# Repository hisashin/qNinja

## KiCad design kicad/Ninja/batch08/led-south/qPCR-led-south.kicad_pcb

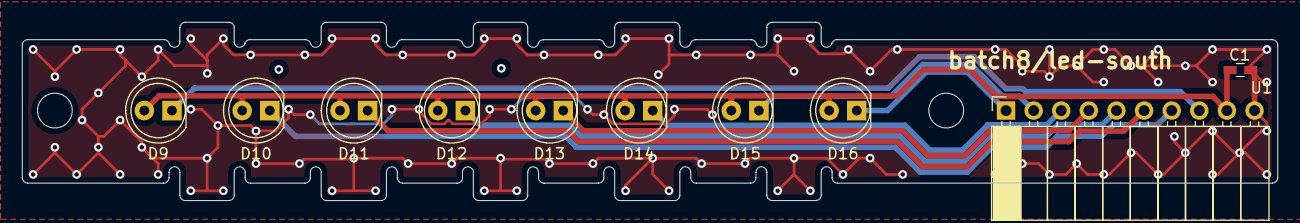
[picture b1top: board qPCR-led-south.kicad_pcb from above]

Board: 2 copper layers, 115.5 x 16.4 mm, 10 parts (0 on the bottom side), 10 nets.

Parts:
C1: C; C_0603_HandSoldering
D9, D10, D11, D12, D13, D14, D15, D16: LED; LED_D5.0mm
U1: Conn_02x05; Socket_Strip_Angled_1x10_Pitch2.54mm

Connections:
GND: C1.2, U1.10
OUT9: D9.1, U1.8
OUT10: D10.1, U1.7
OUT11: D11.1, U1.6
OUT12: D12.1, U1.5
OUT13: D13.1, U1.4
OUT14: D14.1, U1.3
OUT15: D15.1, U1.2
OUT16: D16.1, U1.1
VCC: C1.1, D9.2, D10.2, D11.2, D12.2, D13.2, D14.2, D15.2, D16.2, U1.9

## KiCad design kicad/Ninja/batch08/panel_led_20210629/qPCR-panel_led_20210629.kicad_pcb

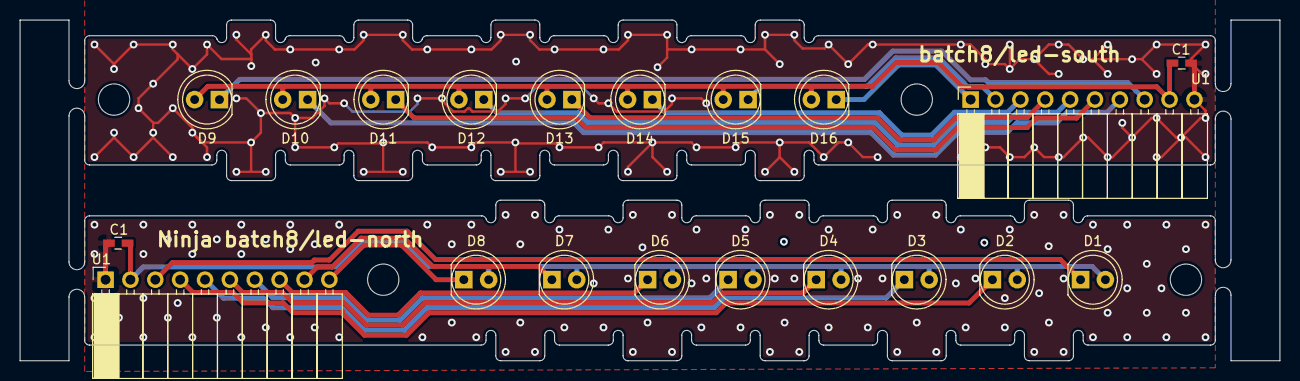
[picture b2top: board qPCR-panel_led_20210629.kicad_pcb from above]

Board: 2 copper layers, 128.7 x 34.8 mm, 20 parts (0 on the bottom side), 18 nets.

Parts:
C1, C1#2: C; C_0603_HandSoldering
D1, D2, D3, D4, D5, D6, D7, D8, D9, D10, D11, D12, D13, D14, D15, D16: LED; LED_D5.0mm
U1, U1#2: Conn_02x05; Socket_Strip_Angled_1x10_Pitch2.54mm

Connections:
GND: C1.2, C1#2.2, U1.1, U1#2.10
OUT1: D1.1, U1.3
OUT2: D2.1, U1.4
OUT3: D3.1, U1.5
OUT4: D4.1, U1.6
OUT5: D5.1, U1.7
OUT6: D6.1, U1.8
OUT7: D7.1, U1.9
OUT8: D8.1, U1.10
OUT9: D9.1, U1#2.8
OUT10: D10.1, U1#2.7
OUT11: D11.1, U1#2.6
OUT12: D12.1, U1#2.5
OUT13: D13.1, U1#2.4
OUT14: D14.1, U1#2.3
OUT15: D15.1, U1#2.2
OUT16: D16.1, U1#2.1
VCC: C1.1, C1#2.1, D1.2, D2.2, D3.2, D4.2, D5.2, D6.2, D7.2, D8.2, D9.2, D10.2, D11.2, D12.2, D13.2, D14.2, D15.2, D16.2, U1.2, U1#2.9

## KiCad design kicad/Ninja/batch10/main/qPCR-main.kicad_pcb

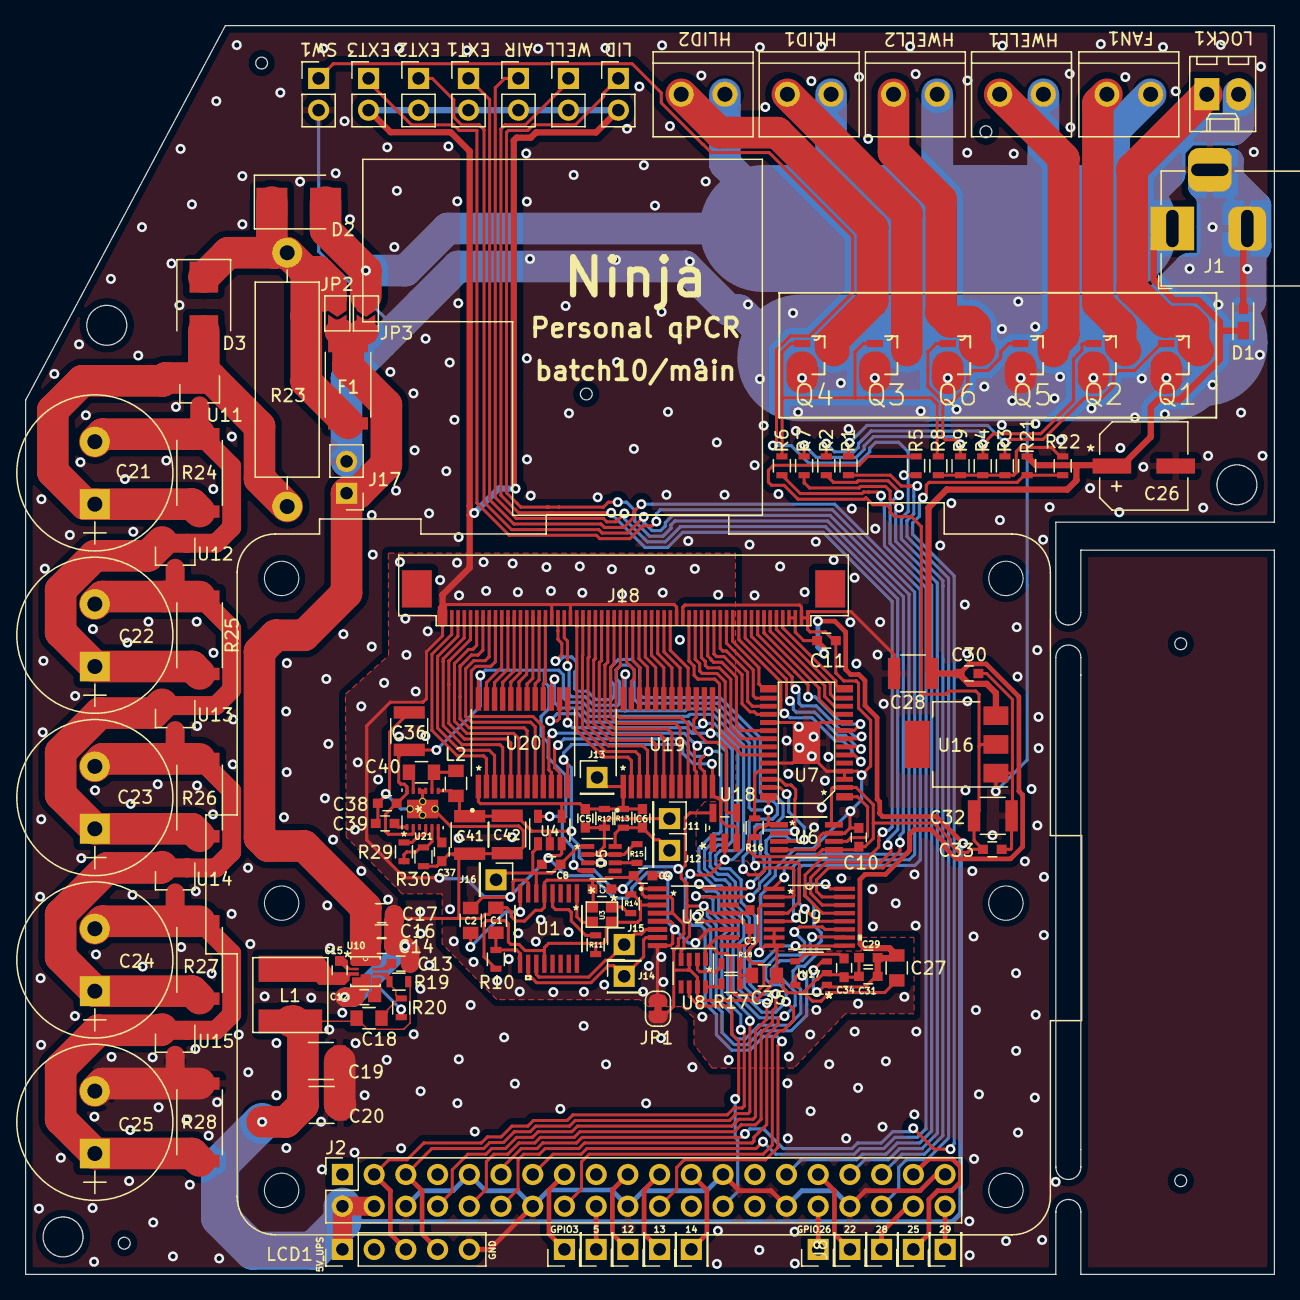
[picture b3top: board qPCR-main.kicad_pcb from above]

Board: 2 copper layers, 100.0 x 100.0 mm, 141 parts (0 on the bottom side), 134 nets.

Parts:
AIR: Conn_01x02_Male; Pin_Header_Straight_1x02_Pitch2.54mm
C1, C2, C27, C35: 4.7uF; C_0805
C3, C4, C7, C8, C10, C11, C14, C15, C29, C30, C33: 0.1uF; C_0603
C5, C6: 22pF; C_0603
C12: 1000pF; C_0603
C13, C37, C38, C39: 1uF; C_0603
C16: 10uF; C_0603
C17, C40: 10uF; C_0805
C18: DNP; C_0805
C19, C20, C28, C32, C36, C41, C42: 22uF; C_1210
C21, C22, C23, C24, C25: 10F2.7V; CP_Radial_D12.5mm_P5.00mm
C26: 100uF; 35TZV100M6.3X8
C31: 0.01uF; C_0603
C34: 100pF; C_0603
D1: D_Schottky; MSS1P3L-M3&slash_89A
D2, D3: D; D_SMB
EXT1, EXT2, EXT3: Conn_01x02_Male; Pin_Header_Straight_1x02_Pitch2.54mm
F1: Fuse; R_2512
FAN1: Screw_Terminal_01x02; TB_SeeedOPL_320110028
HLID1, HLID2: Screw_Terminal_01x02; TB_SeeedOPL_320110028
HWELL1, HWELL2: Screw_Terminal_01x02; TB_SeeedOPL_320110028
J1: Barrel_Jack_Switch; BarrelJack_Horizontal
J2: Raspberry_Pi_3A_Plus_wpi; Raspberry_Pi_3A+_3B+_4B_Zero_FaceDown_HDMI-R
J3, J4, J5, J6, J7, J8, J9, J10, J11, J12, J13, J14, J15, J16, J19, J20: Conn_01x01_Male; Pin_Header_Straight_1x01_Pitch2.54mm
J17: Conn_01x02_Male; Pin_Header_Straight_1x02_Pitch2.54mm
J18: Conn_01x60_Male; FFC_60_Ali_HUISHUNFA
JP1: SolderJumper_2_Bridged; SolderJumper-2_P1.3mm_Bridged_RoundedPad1.0x1.5mm
JP2, JP3: Jumper; SolderJumper-2_P1.3mm_Open_TrianglePad1.0x1.5mm
L1: 3.3uH; VLS6045EX-3R3N
L2: 2.2uH; C_0805
LCD1: RPI_LCD_TOUCH_7INCH; Pin_Header_Straight_1x05_Pitch2.54mm
LID: Conn_01x02_Male; Pin_Header_Straight_1x02_Pitch2.54mm
LOCK1: Conn_01x02_Male; Molex_KK-6410-02_02x2.54mm_Straight
Q1, Q2, Q3, Q4, Q5, Q6: Q_NMOS_GSD; SOT95P240X112-3N
R1, R2, R6, R7: 150; R_0603
R3, R4, R5, R8, R9, R16, R18, R21: 47k; R_0603
R10, R11, R14, R15, R17, R20, R22: 10k; R_0603
R12: 10M; R_0603
R13: 1M; R_0603
R19: 56k; R_0603
R23: 8.2Ω 3W; R_Axial_DIN0516_L15.5mm_D5.0mm_P20.32mm_Horizontal
R24, R25, R26, R27, R28: 1k2W; R_2512
R29: 39k; R_0603
R30: 150k; R_0603
SW1: SW_Reed; Pin_Header_Straight_1x02_Pitch2.54mm
U1: ADA2200ARUZ
U2: ADS122C04IPWR
U3: COM1305-0.032768-EXT-T-TR; ASDK-32.768KHZ-LRT
U4: LMP7717MF_NOPB; SOT-23-5
U5, U8: TS12A12511DCNR; SOT-23-8
U6: MCP4551T-503E/MS; MCP4551T-502E&slash_MS
U7: PCA9955B
U9: SN74LV4051APWR
U10: UMMP008Z2020_ROM; BD9D323QWZ-E2
U11, U12, U13, U14, U15: TL431DBZ; SOT-23
U16: CJT1117-3.3; SOT-223
U17: AP2210K-3.3TRG1
U18: SN74LVC1GU04DCKR; SN74LVC1GU04DBVR
U19, U20: CD74HC4067M96; SOP65P780X200-24N
U21: DRR0012C; TPS63710DRRR
WELL: Conn_01x02_Male; Pin_Header_Straight_1x02_Pitch2.54mm

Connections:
3V3A: C3.1, C35.1, R17.1, R18.1, U2.9, U2.12, U17.5
3V3D: C3.2, C7.1, C10.1, C32.1, C33.1, C36.1, C38.1, R5.1, R10.2, R11.2, R14.2, R16.2, U1.12, U2.3, U2.13, U3.4, U4.5, U5.4, U6.1, U6.5, U6.8, U7.2, U7.28, U8.4, U9.16, U16.2, U18.5, U19.24, U20.24, U21.2, U21.12
5V_UPS: C11.1, C18.2, C19.2, C20.2, J2.2, J2.4, J18.3, J18.4, L1.1, LCD1.1, R19.1
12V: C26.1, C27.1, C28.1, C29.1, C30.1, C31.1, D1.1, D2.2, FAN1.1, HLID1.1, HLID2.1, HWELL1.1, HWELL2.1, J1.1, JP3.1, LOCK1.2, R21.1, U16.3, U17.1, U17.3
12V_UPS: C14.2, C16.2, C17.2, F1.1, J17.1, JP2.2, JP3.2, U10.1, U10.8
-1V: C41.1, C42.1, L2.2, R15.2, U4.2, U5.3, U5.7, U18.3, U19.12, U20.12, U21.7
/5V_UPS/FB: C18.1, R19.2, R20.1, U10.6
/5V_UPS/SS: C12.2, U10.5
/FAN: J2.29, R2.2
/GPIO3: J2.15, J3.1
/GPIO5: J2.18, J4.1
/GPIO12: J2.19, J5.1
/GPIO13: J2.21, J6.1
/GPIO14: J2.23, J7.1
/GPIO22: J2.31, J8.1
/GPIO25: J2.37, J19.1
/GPIO26: J2.32, J9.1
/GPIO28: J2.38, J10.1
/GPIO29: J2.40, J20.1
/LID_HEATER: J2.13, R6.2
/Photo/AMP_GAIN_SW: R15.1, U5.6
/Photo/AMP_OUT: C8.2, J16.1, U1.6, U4.1, U5.1
/Photo/GAIN_LARGE: C5.1, J11.1, R12.2, U5.2
/Photo/GAIN_SMALL: C6.1, J12.1, R13.2, U5.8
/Photo/PHOTO_OUT_N: J14.1, U1.10, U2.7
/Photo/PHOTO_OUT_P: J15.1, U1.11, U2.6
/PhotoLED/LED_IREF: U6.6, U7.1
/PhotoMUX/MUX_SELECT_INV: U18.4, U19.15
/PhotoMUX/N_PD_OUT1: J18.43, U20.16
/PhotoMUX/N_PD_OUT2: J18.44, U20.17
/PhotoMUX/N_PD_OUT3: J18.45, U20.18
/PhotoMUX/N_PD_OUT4: J18.46, U20.19
/PhotoMUX/N_PD_OUT5: J18.47, U20.20
/PhotoMUX/N_PD_OUT6: J18.48, U20.21
/PhotoMUX/N_PD_OUT7: J18.49, U20.22
/PhotoMUX/N_PD_OUT8: J18.50, U20.23
/PhotoMUX/N_PD_OUT9: J18.51, U20.9
/PhotoMUX/N_PD_OUT10: J18.52, U20.8
/PhotoMUX/N_PD_OUT11: J18.53, U20.7
/PhotoMUX/N_PD_OUT12: J18.54, U20.6
/PhotoMUX/N_PD_OUT13: J18.55, U20.5
/PhotoMUX/N_PD_OUT14: J18.56, U20.4
/PhotoMUX/N_PD_OUT15: J18.57, U20.3
/PhotoMUX/N_PD_OUT16: J18.58, U20.2
/PhotoMUX/S_PD_OUT1: J18.38, U19.2
/PhotoMUX/S_PD_OUT2: J18.37, U19.3
/PhotoMUX/S_PD_OUT3: J18.36, U19.4
/PhotoMUX/S_PD_OUT4: J18.35, U19.5
/PhotoMUX/S_PD_OUT5: J18.34, U19.6
/PhotoMUX/S_PD_OUT6: J18.33, U19.7
/PhotoMUX/S_PD_OUT7: J18.32, U19.8
/PhotoMUX/S_PD_OUT8: J18.31, U19.9
/PhotoMUX/S_PD_OUT9: J18.30, U19.23
/PhotoMUX/S_PD_OUT10: J18.29, U19.22
/PhotoMUX/S_PD_OUT11: J18.28, U19.21
/PhotoMUX/S_PD_OUT12: J18.27, U19.20
/PhotoMUX/S_PD_OUT13: J18.26, U19.19
/PhotoMUX/S_PD_OUT14: J18.25, U19.18
/PhotoMUX/S_PD_OUT15: J18.24, U19.17
/PhotoMUX/S_PD_OUT16: J18.23, U19.16
/WELL_HEATER: J2.33, R7.2
CLKIN: U1.1, U3.3
DLOCK: J2.36, R1.2
DOPEN: J2.35, R5.2, SW1.1
GND: C1.2, C4.2, C7.2, C10.2, C11.2, C12.1, C13.1, C14.1, C16.1, C17.1, C19.1, C20.1, C25.2, C26.2, C27.2, C28.2, C29.2, C30.2, C31.2, C32.2, C33.2, C34.2, C35.2, C36.2, C37.2, C38.2, C39.2, C41.2, C42.2, D1.2, J1.2, J1.3, J2.6, J2.9, J2.14, J2.20, J2.25, J2.30, J2.34, J2.39, J17.2, J18.1, J18.2, J18.21, JP1.1, LCD1.5, Q1.2, Q2.2, Q3.2, Q4.2, Q5.2, Q6.2, R3.1, R4.1, R8.1, R9.1, R20.2, R22.2, R28.1, R30.2, SW1.2, U1.5, U2.1, U2.2, U2.4, U3.2, U6.4, U6.7, U7.3, U7.4, U7.10, U7.19, U7.24, U7.29, U8.3, U8.7, U9.6, U9.7, U9.8, U10.4, U10.9, U15.3, U16.1, U17.2, U21.9, U21.10, U21.13, U21.V
GNDA: AIR.2, C2.2, C4.1, C8.1, EXT1.2, EXT2.2, EXT3.2, J18.22, J18.39, J18.42, J18.59, J18.60, JP1.2, LID.2, U1.7, U2.5, U2.8, U2.11, U4.3, WELL.2
I2C_SCL: J2.5, LCD1.4, U2.16, U6.2, U7.26
I2C_SDA: J2.3, LCD1.3, U2.15, U6.3, U7.27
MUX_S0: J2.16, U9.11, U19.10, U20.10
MUX_S1: J2.12, U9.10, U19.11, U20.11
MUX_S2: J2.10, U9.9, U19.14, U20.14
MUX_S3: J2.8, U19.13, U20.13
MUX_SELECT: J2.22, U18.2, U20.15
N_LED_OUT1: J18.20, U7.23
N_LED_OUT2: J18.19, U7.22
N_LED_OUT3: J18.18, U7.21
N_LED_OUT4: J18.17, U7.20
N_LED_OUT5: J18.16, U7.18
N_LED_OUT6: J18.15, U7.17
N_LED_OUT7: J18.14, U7.16
N_LED_OUT8: J18.13, U7.15
unnamed: C1.1, R10.1, U1.9
unnamed: C2.1, U1.8
unnamed: C13.2, U10.7
unnamed: C15.1, L1.2, U10.3
unnamed: C15.2, U10.2
unnamed: C21.1, D3.2, R23.1, R24.2, U11.1, U11.2
unnamed: C21.2, C22.1, R24.1, R25.2, U11.3, U12.1, U12.2
unnamed: C22.2, C23.1, R25.1, R26.2, U12.3, U13.1, U13.2
unnamed: C23.2, C24.1, R26.1, R27.2, U13.3, U14.1, U14.2
unnamed: C24.2, C25.1, R27.1, R28.2, U14.3, U15.1, U15.2
unnamed: C34.1, U17.4
unnamed: C37.1, U21.6
unnamed: C39.1, U21.1
unnamed: C40.1, U21.11
unnamed: C40.2, L2.1, U21.8
unnamed: D2.1, D3.1, F1.2, JP2.1, R23.2
unnamed: FAN1.2, Q2.3
unnamed: HLID1.2, Q3.3
unnamed: HLID2.2, Q4.3
unnamed: HWELL1.2, Q5.3
unnamed: HWELL2.2, Q6.3
unnamed: LOCK1.1, Q1.3
unnamed: Q1.1, R1.1, R3.2
unnamed: Q2.1, R2.1, R4.2
unnamed: Q3.1, Q4.1, R6.1, R8.2
unnamed: Q5.1, Q6.1, R7.1, R9.2
unnamed: R11.1, U1.4
unnamed: R14.1, U3.1
unnamed: R16.1, U7.25
unnamed: R17.2, U8.8
unnamed: R18.2, U8.2
unnamed: R29.1, U21.4
unnamed: R29.2, R30.1, U21.5
PD_MUX_OUT: C5.2, C6.2, J13.1, R12.1, R13.1, U4.4, U19.1, U20.1
PD_TH1: J18.40, U9.2
PD_TH2: J18.41, U9.4
S_LED_OUT1: J18.12, U7.6
S_LED_OUT2: J18.11, U7.7
S_LED_OUT3: J18.10, U7.8
S_LED_OUT4: J18.9, U7.9
S_LED_OUT5: J18.8, U7.11
S_LED_OUT6: J18.7, U7.12
S_LED_OUT7: J18.6, U7.13
S_LED_OUT8: J18.5, U7.14
THERM_AIR: AIR.1, U9.14
THERM_EXT1: EXT1.1, U9.12
THERM_EXT2: EXT2.1, U9.1
THERM_EXT3: EXT3.1, U9.5
THERM_LID: LID.1, U9.15
THERM_MUX_OUT: U2.10, U8.1, U9.3
THERM_R_SWITCH: J2.26, U8.6
THERM_WELL: U9.13, WELL.1
VIN_SENSE: J2.11, R21.2, R22.1

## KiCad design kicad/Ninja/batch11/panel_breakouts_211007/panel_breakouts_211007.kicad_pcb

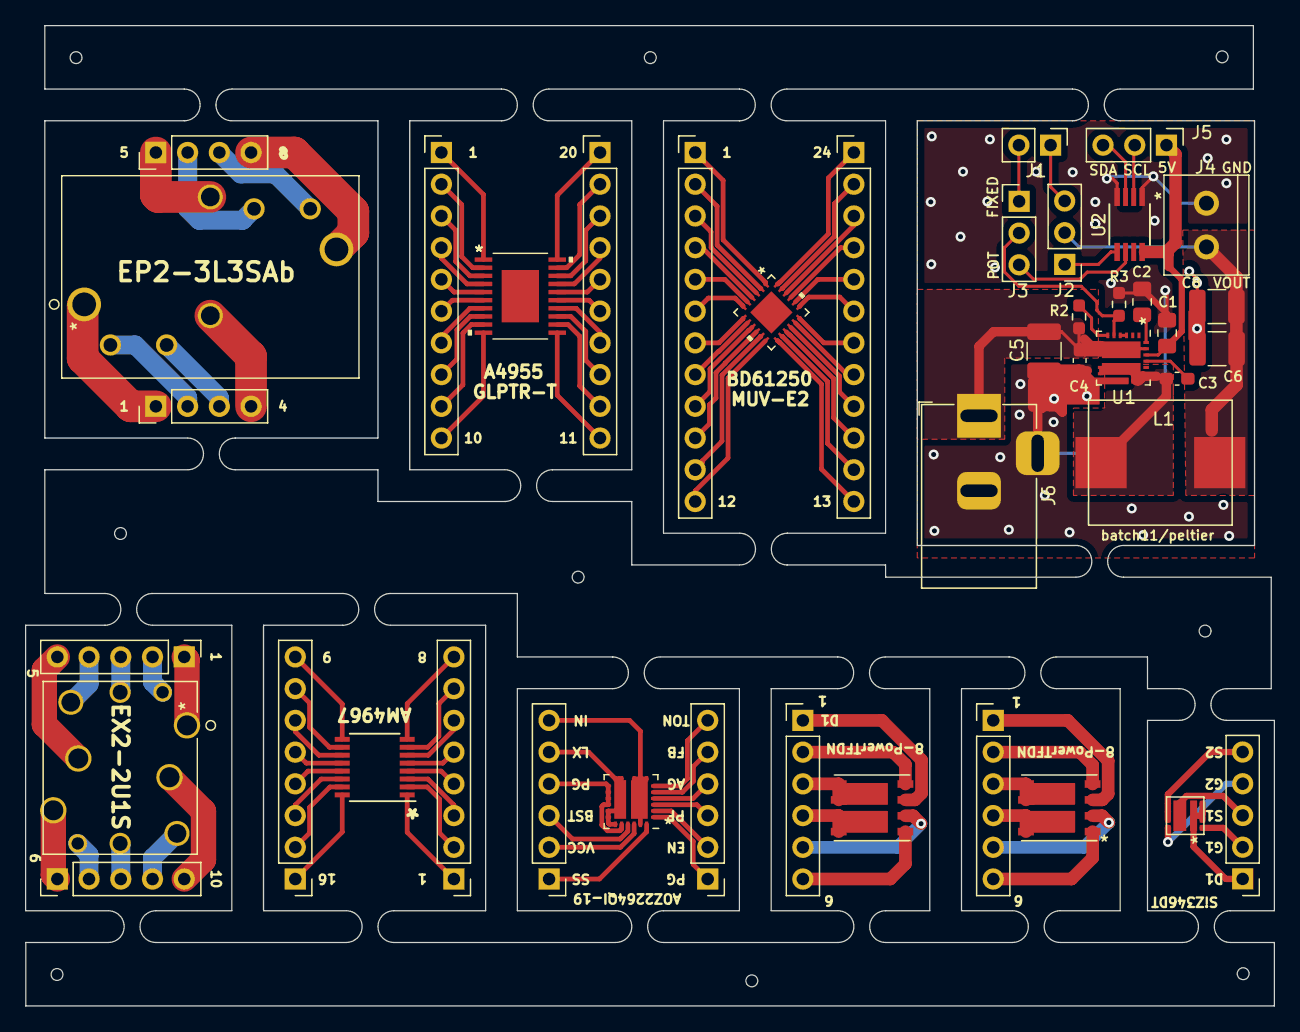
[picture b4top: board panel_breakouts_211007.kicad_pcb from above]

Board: 2 copper layers, 100.0 x 78.5 mm, 42 parts (0 on the bottom side), 122 nets.

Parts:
C1, C2: 10uF; C_0805_2012Metric_Pad1.18x1.45mm_HandSolder
C3: 0.1uF; C_0603_1608Metric_Pad1.08x0.95mm_HandSolder
C4: 1uF; C_0603_1608Metric_Pad1.08x0.95mm_HandSolder
C5: 22uF; C_1210_3225Metric_Pad1.33x2.70mm_HandSolder
C6, C8: 47uF; C_1210_3225Metric_Pad1.33x2.70mm_HandSolder
J1, J4: Conn_01x04_Male; Pin_Header_Straight_1x04_Pitch2.54mm
J1#2: Conn_01x02_Female; Pin_Header_Straight_1x02_Pitch2.54mm
J2, J3, J13: Conn_01x05_Male; Pin_Header_Straight_1x05_Pitch2.54mm
J2#2, J3#2, J5#2: Conn_01x03_Male; Pin_Header_Straight_1x03_Pitch2.54mm
J4#2: Screw_Terminal_01x02; TB_SeeedOPL_320110028
J5, J6: Conn_01x10_Male; Pin_Header_Straight_1x10_Pitch2.54mm
J6#2: Barrel_Jack_Switch; BarrelJack_Horizontal
J7, J8: Conn_01x08_Male; Pin_Header_Straight_1x08_Pitch2.54mm
J9, J10: Conn_01x12_Male; Pin_Header_Straight_1x12_Pitch2.54mm
J11, J12, J14, J15: Conn_01x06_Male; Pin_Header_Straight_1x06_Pitch2.54mm
K1: EX2-2U1S
K2: EP2-3L3SAb
L1: 3.3uH; 104CDMCCDS-2R2MC
R2: 150k; R_0603_1608Metric_Pad0.98x0.95mm_HandSolder
R3: 5k; R_0603_1608Metric_Pad0.98x0.95mm_HandSolder
U1: A4955GLPTR-T
U1#2, U7: AOZ2264QI-19
U2: MCP4551T-104; MCP4551T-502E&slash_MS
U2#2: AM4967; SSOP-16_3.9x4.9mm_Pitch0.635mm
U3: BD61250MUV-E2‎; BD61250MUV-E2
U4: 8-PowerTDFN-PN; 8-PowerTDFN
U5: 8-PowerTDFN-NN; 8-PowerTDFN
U6: SiZ346DT

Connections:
5V: C1.1, J5#2.1, U1#2.2, U1#2.21, U2.8
12V: C4.1, C5.1, J6#2.1, R2.1, U1#2.7, U1#2.8, U1#2.9, U1#2.22
/A1: J1.1, K2.1
/A2: J1.2, K2.2
/A3: J1.3, K2.3
/A4: J1.4, K2.4
/A5: J4.1, K2.5
/A6: J4.2, K2.6
/A7: J4.3, K2.7
/A8: J4.4, K2.8
/B1: J2.1, K1.1
/B2: J2.2, K1.2
/B3: J2.3, K1.3
/B4: J2.4, K1.4
/B5: J2.5, K1.5
/B6: J3.1, K1.6
/B7: J3.2, K1.7
/B8: J3.3, K1.8
/B9: J3.4, K1.9
/B10: J3.5, K1.10
/C1: J5.1, U1.1
/C2: J5.2, U1.2
/C3: J5.3, U1.3
/C4: J5.4, U1.4
/C5: J5.5, U1.5
/C6: J5.6, U1.6
/C7: J5.7, U1.7
/C8: J5.8, U1.8
/C9: J5.9, U1.9
/C10: J5.10, U1.10
/C11: J6.10, U1.11
/C12: J6.9, U1.12
/C13: J6.8, U1.13
/C14: J6.7, U1.14
/C15: J6.6, U1.15
/C16: J6.5, U1.16
/C17: J6.4, U1.17
/C18: J6.3, U1.18
/C19: J6.2, U1.19
/C20: J6.1, U1.20
/D1: J7.1, U2#2.1
/D2: J7.2, U2#2.2
/D3: J7.3, U2#2.3
/D4: J7.4, U2#2.4
/D5: J7.5, U2#2.5
/D6: J7.6, U2#2.6
/D7: J7.7, U2#2.7
/D8: J7.8, U2#2.8
/D9: J8.8, U2#2.9
/D10: J8.7, U2#2.10
/D11: J8.6, U2#2.11
/D12: J8.5, U2#2.12
/D13: J8.4, U2#2.13
/D14: J8.3, U2#2.14
/D15: J8.2, U2#2.15
/D16: J8.1, U2#2.16
/E1: J9.1, U3.1
/E2: J9.2, U3.2
/E3: J9.3, U3.3
/E4: J9.4, U3.4
/E5: J9.5, U3.5
/E6: J9.6, U3.6
/E7: J9.7, U3.7
/E8: J9.8, U3.8
/E9: J9.9, U3.9
/E10: J9.10, U3.10
/E11: J9.11, U3.11
/E12: J9.12, U3.12
/E13: J10.12, U3.13
/E14: J10.11, U3.14
/E15: J10.10, U3.15
/E16: J10.9, U3.16
/E17: J10.8, U3.17
/E18: J10.7, U3.18
/E19: J10.6, U3.19
/E20: J10.5, U3.20
/E21: J10.4, U3.21
/E22: J10.3, U3.22
/E23: J10.2, U3.23
/E24: J10.1, U3.24
/F1: J11.1, U4.3
/F2: J11.2, U4.4
/F3: J11.3, U4.5, U4.6
/F4: J11.4, U4.7, U4.8
/F5: J11.5, U4.2
/F6: J11.6, U4.1
/FB_RES_B: J3#2.2, R3.1, U1#2.5
/G1: J12.1, U5.3
/G2: J12.2, U5.4
/G3: J12.3, U5.5, U5.6
/G4: J12.4, U5.7, U5.8
/G5: J12.5, U5.2
/G6: J12.6, U5.1
/H1: J13.1, U6.2, U6.3, U6.4, U6.10
/H2: J13.2, U6.1
/H3: J13.3, U6.9
/H4: J13.4, U6.8
/H5: J13.5, U6.5, U6.6, U6.7
/I1: J14.1, U7.1
/I2: J14.2, U7.2
/I3: J14.3, U7.3
/I4: J14.4, U7.4
/I5: J14.5, U7.5
/I6: J14.6, U7.6
/I7: J15.6, U7.7, U7.8, U7.9, U7.22
/I10: J15.5, U7.10, U7.11, U7.16, U7.17, U7.18
/I12: J15.4, U7.12, U7.13, U7.14, U7.15, U7.19
/I20: J15.3, U7.20
/I21: J15.2, U7.21
/I23: J15.1, U7.23
/POT_RES_A: J2#2.1, U2.5
/POT_RES_B: J3#2.3, U2.6
GND: C1.2, C2.2, C4.2, C5.2, C6.2, C8.2, J4#2.2, J6#2.2, J6#2.3, R3.2, U1#2.3, U1#2.4, U1#2.12, U1#2.13, U1#2.14, U1#2.15, U1#2.19, U2.1, U2.4
I2C_SCL: J5#2.2, U2.2
I2C_SDA: J5#2.3, U2.3
unnamed: C2.1, U1#2.23
unnamed: C3.1, U1#2.20
unnamed: C3.2, L1.1, U1#2.10, U1#2.11, U1#2.16, U1#2.17, U1#2.18
unnamed: J1#2.1, J2#2.3
unnamed: J1#2.2, J3#2.1
unnamed: R2.2, U1#2.6
REG_OUT: C6.1, C8.1, J2#2.2, J4#2.1, L1.2

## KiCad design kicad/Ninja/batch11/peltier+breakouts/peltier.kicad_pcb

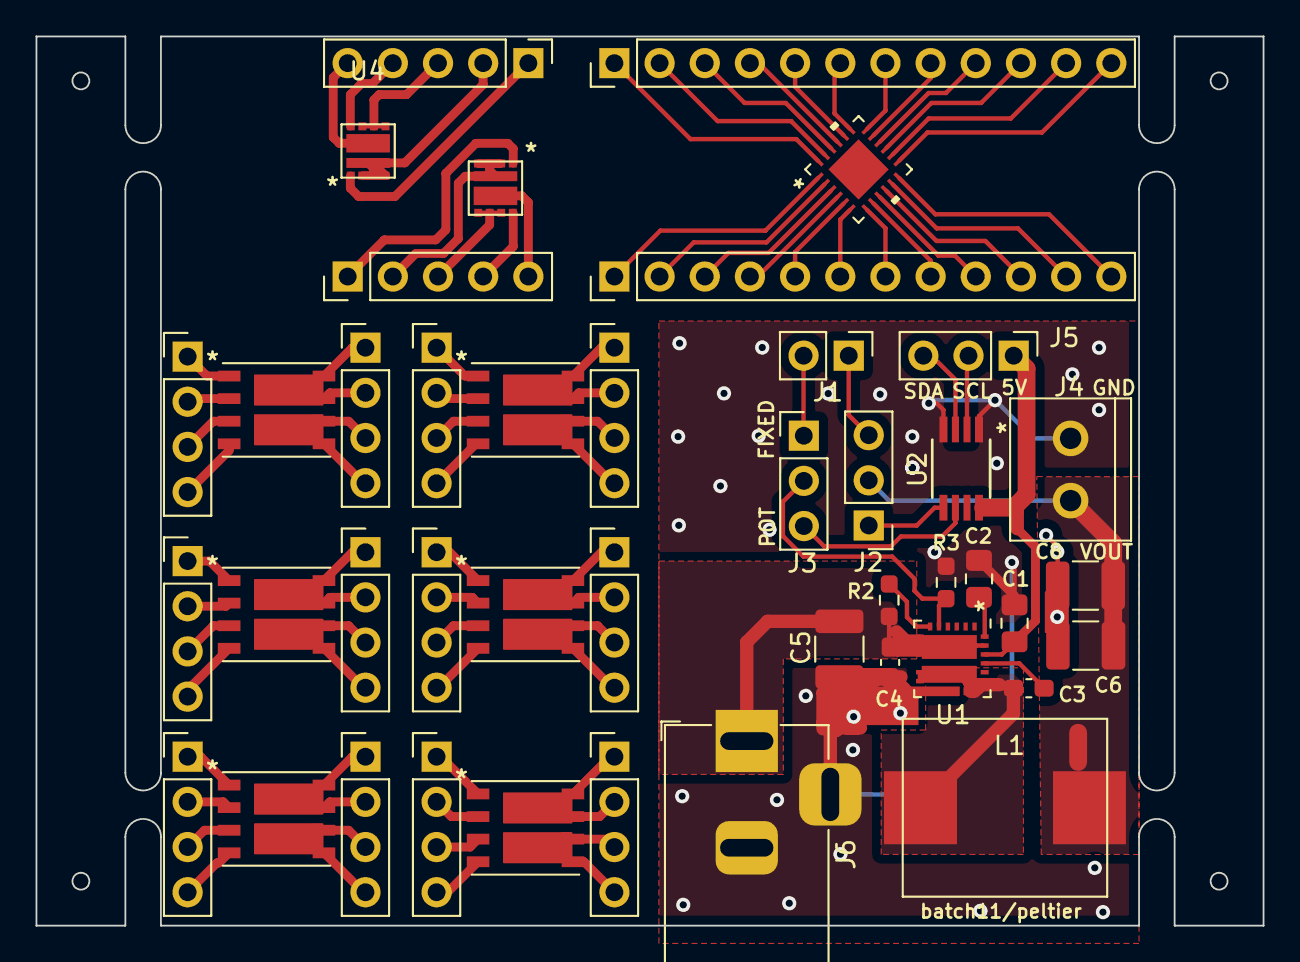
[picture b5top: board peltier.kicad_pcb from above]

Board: 2 copper layers, 69.0 x 50.0 mm, 43 parts (0 on the bottom side), 97 nets.

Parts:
C1, C2: 10uF; C_0805_2012Metric_Pad1.18x1.45mm_HandSolder
C3: 0.1uF; C_0603_1608Metric_Pad1.08x0.95mm_HandSolder
C4: 1uF; C_0603_1608Metric_Pad1.08x0.95mm_HandSolder
C5: 22uF; C_1210_3225Metric_Pad1.33x2.70mm_HandSolder
C6, C8: 47uF; C_1210_3225Metric_Pad1.33x2.70mm_HandSolder
J1: Conn_01x02_Female; Pin_Header_Straight_1x02_Pitch2.54mm
J2, J3, J5: Conn_01x03_Male; Pin_Header_Straight_1x03_Pitch2.54mm
J4: Screw_Terminal_01x02; TB_SeeedOPL_320110028
J6: Barrel_Jack_Switch; BarrelJack_Horizontal
J7, J8, J9, J10, J11, J12, J13, J14, J18, J19, J20, J21: Conn_01x04_Male; Pin_Header_Straight_1x04_Pitch2.54mm
J15, J22: Conn_01x05_Male; Pin_Header_Straight_1x05_Pitch2.54mm
J16, J17: Conn_01x12_Male; Pin_Header_Straight_1x12_Pitch2.54mm
L1: 3.3uH; 104CDMCCDS-2R2MC
R2: 150k; R_0603_1608Metric_Pad0.98x0.95mm_HandSolder
R3: 5k; R_0603_1608Metric_Pad0.98x0.95mm_HandSolder
U1: AOZ2264QI-19
U2: MCP4551T-104; MCP4551T-502E&slash_MS
U3, U6, U7, U8, U9, U10: 8-PowerTDFN-NN; 8-PowerTDFN
U4, U11: SiZ346DT
U5: BD61250MUV-E2‎; BD61250MUV-E2

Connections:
5V: C1.1, J5.1, U1.2, U1.21, U2.8
12V: C4.1, C5.1, J6.1, R2.1, U1.7, U1.8, U1.9, U1.22
/A1: J15.1, U4.1
/A2: J15.2, U4.2, U4.3, U4.4, U4.10
/A5: J15.3, U4.5, U4.6, U4.7
/A8: J15.4, U4.8
/A9: J15.5, U4.9
/B1: J16.1, U5.1
/B2: J16.2, U5.2
/B3: J16.3, U5.3
/B4: J16.4, U5.4
/B5: J16.5, U5.5
/B6: J16.6, U5.6
/B7: J16.7, U5.7
/B8: J16.8, U5.8
/B9: J16.9, U5.9
/B10: J16.10, U5.10
/B11: J16.11, U5.11
/B12: J16.12, U5.12
/B13: J17.12, U5.13
/B14: J17.11, U5.14
/B15: J17.10, U5.15
/B16: J17.9, U5.16
/B17: J17.8, U5.17
/B18: J17.7, U5.18
/B19: J17.6, U5.19
/B20: J17.5, U5.20
/B21: J17.4, U5.21
/B22: J17.3, U5.22
/B23: J17.2, U5.23
/B24: J17.1, U5.24
/C1: J22.1, U11.1
/C2: J22.2, U11.2, U11.3, U11.4, U11.10
/C5: J22.3, U11.5, U11.6, U11.7
/C8: J22.4, U11.8
/C9: J22.5, U11.9
/FB_RES_B: J3.2, R3.1, U1.5
/POT_RES_A: J2.1, U2.5
/POT_RES_B: J3.3, U2.6
GND: C1.2, C2.2, C4.2, C5.2, C6.2, C8.2, J4.2, J6.2, J6.3, R3.2, U1.3, U1.4, U1.12, U1.13, U1.14, U1.15, U1.19, U2.1, U2.4
I2C_SCL: J5.2, U2.2
I2C_SDA: J5.3, U2.3
unnamed: C2.1, U1.23
unnamed: C3.1, U1.20
unnamed: C3.2, L1.1, U1.10, U1.11, U1.16, U1.17, U1.18
unnamed: J1.1, J2.3
unnamed: J1.2, J3.1
unnamed: J7.1, U3.1
unnamed: J7.2, U3.2
unnamed: J7.3, U3.3
unnamed: J7.4, U3.4
unnamed: J8.1, U6.1
unnamed: J8.2, U6.2
unnamed: J8.3, U6.3
unnamed: J8.4, U6.4
unnamed: J9.1, U3.8
unnamed: J9.2, U3.7
unnamed: J9.3, U3.6
unnamed: J9.4, U3.5
unnamed: J10.1, U6.8
unnamed: J10.2, U6.7
unnamed: J10.3, U6.6
unnamed: J10.4, U6.5
unnamed: J11.1, U7.1
unnamed: J11.2, U7.2
unnamed: J11.3, U7.3
unnamed: J11.4, U7.4
unnamed: J12.1, U8.1
unnamed: J12.2, U8.2
unnamed: J12.3, U8.3
unnamed: J12.4, U8.4
unnamed: J13.1, U7.8
unnamed: J13.2, U7.7
unnamed: J13.3, U7.6
unnamed: J13.4, U7.5
unnamed: J14.1, U8.8
unnamed: J14.2, U8.7
unnamed: J14.3, U8.6
unnamed: J14.4, U8.5
unnamed: J18.1, U9.1
unnamed: J18.2, U9.2
unnamed: J18.3, U9.3
unnamed: J18.4, U9.4
unnamed: J19.1, U9.8
unnamed: J19.2, U9.7
unnamed: J19.3, U9.6
unnamed: J19.4, U9.5
unnamed: J20.1, U10.1
unnamed: J20.2, U10.2
unnamed: J20.3, U10.3
unnamed: J20.4, U10.4
unnamed: J21.1, U10.8
unnamed: J21.2, U10.7
unnamed: J21.3, U10.6
unnamed: J21.4, U10.5
unnamed: R2.2, U1.6
REG_OUT: C6.1, C8.1, J2.2, J4.1, L1.2

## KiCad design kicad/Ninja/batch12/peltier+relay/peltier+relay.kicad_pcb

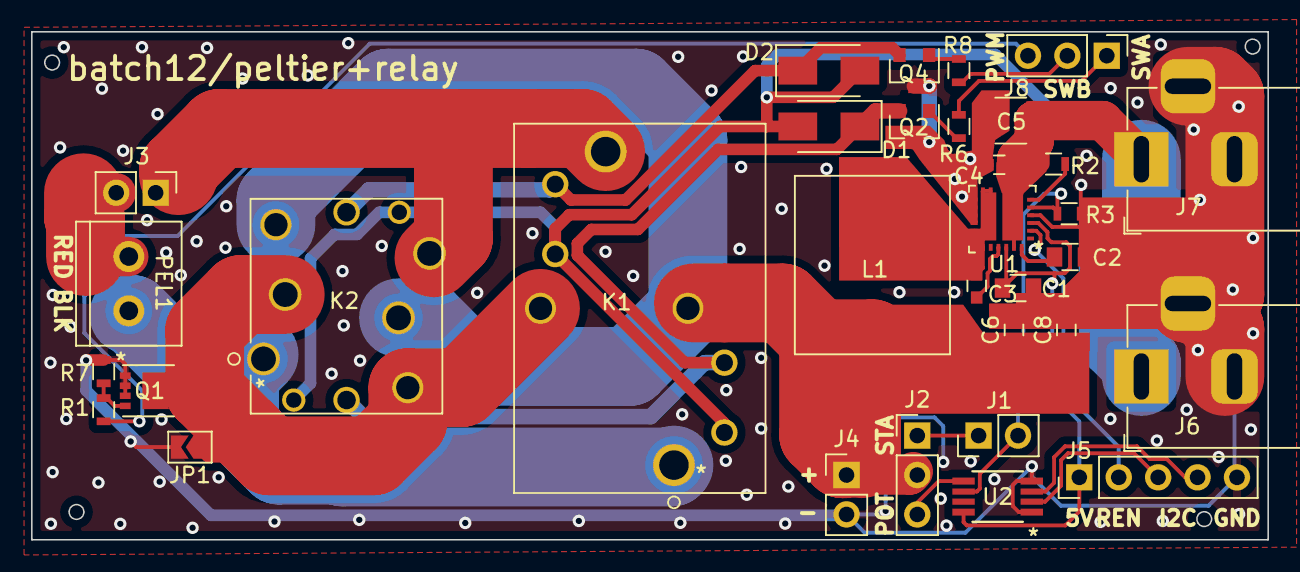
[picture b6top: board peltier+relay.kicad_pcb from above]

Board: 2 copper layers, 79.7 x 32.7 mm, 33 parts (0 on the bottom side), 26 nets.

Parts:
C1, C2: 10uF; C_0805
C3, C6: 0.1uF; C_0603
C4, C8: 1uF; C_0603
C5: 22uF; C_1210
D1, D2: DIODE; D_SMA
J1, J3, J4: Conn_01x02_Female; Pin_Header_Straight_1x02_Pitch2.54mm
J2, J8: Conn_01x03_Male; Pin_Header_Straight_1x03_Pitch2.54mm
J5: Conn_01x05_Male; Pin_Header_Straight_1x05_Pitch2.54mm
J6, J7: Barrel_Jack_Switch; BarrelJack_Horizontal
JP1: Jumper; SolderJumper-2_P1.3mm_Open_TrianglePad1.0x1.5mm
K1: EP2-3L3SAb
K2: EX2-2U1S
L1: 3.3uH; 104CDMCCDS-2R2MC
PEL1: Screw_Terminal_01x02; TB_SeeedOPL_320110028
Q1: 8-PowerVDFN-N; 8-PowerVDFN
Q2, Q4: Q_NPN_BCE; SOT-23
R1: 150; R_0603
R2: 60k; R_0603
R3: 5k; R_0603
R6, R8: 10k; R_0603
R7: 47k; R_0603
U1: AOZ2264QI-19
U2: MCP4551T-104; MCP4551T-502E&slash_MS

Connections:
5V: C1.1, J5.1, U1.3, U1.21, U2.8
12V: C4.1, C5.1, D1.2, D2.2, J6.1, J7.1, K1.2, K1.6, K2.2, K2.7, R2.1, U1.7, U1.8, U1.9, U1.22
/PEL1: D1.1, K1.3, K2.3, Q2.2
/PEL2: JP1.1, K1.5, K2.4, K2.10, Q1.5, Q1.6, Q1.7, Q1.8
/PEL3: D2.1, K1.7, K2.8, Q4.2
/PEL_BLK: K1.1, K2.1, PEL1.2
/PEL_RED: J3.1, K1.8, K2.6
/POT_RES_A: J2.3, U2.5
GND: C1.2, C2.2, C4.2, C5.2, C6.2, C8.2, J4.2, J5.5, J6.2, J6.3, J7.2, J7.3, JP1.2, Q1.1, Q1.2, Q1.3, Q2.3, Q4.3, R3.2, R7.1, U1.4, U1.12, U1.13, U1.14, U1.15, U1.19, U2.1, U2.4
I2C_SCL: J5.3, U2.2
I2C_SDA: J5.4, U2.3
unnamed: C2.1, U1.23
unnamed: C3.1, U1.20
unnamed: J1.1, J2.1
unnamed: J3.2, PEL1.1
unnamed: Q1.4, R1.1, R7.2
unnamed: Q2.1, R6.1
unnamed: Q4.1, R8.2
unnamed: R2.2, U1.6
PEL_PWM: J8.3, R1.2
PEL_SWA: J8.1, R6.2
PEL_SWB: J8.2, R8.1
REG_EN: J5.2, U1.2
REG_FB: J1.2, R3.1, U1.5, U2.6
REG_LX: C3.2, L1.1, U1.10, U1.11, U1.16, U1.17, U1.18
REG_OUT: C6.1, C8.1, J2.2, J4.1, K1.4, K2.5, K2.9, L1.2

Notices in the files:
parts and their libraries:
Copyright 2021 Accelerated Designs. All rights reserved.
Copyright 2016 Accelerated Designs. All rights reserved.
